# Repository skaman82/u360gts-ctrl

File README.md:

# u360gts-ctrl
u360gts Extension for the Mini-Case

This has the following functions:

• Turn ON/OFF the VTX</br>
• SmartAudio channel control (SA 2+ Version not supported, for unify nano you will need a 10k pull-down resistor on SA)</br>
• Battery monitoring</br>
• Controlls pan servo manually to allow to get to the screws of the case</br>
• Automatic parking mode to align the tracker again</br>

# PARTS
• Provided PCB

• Arduino Pro Micro (Leonardo) 3.3V
https://de.aliexpress.com/item/32992577032.html
If you have a 5V version, just replace the VREG on the board with this one: MIC5205-3.3YM5-TR

• 1206 4.7k resistor (R3)</br>
• 1206 27k resistor (R1)</br>
• 1206 100nf capacitor (C3)</br>
• 4x 0603 10k resistor (R2, R4, R5, R6)</br>
• 0603 1k resistor (R7)</br>
• IRLML6402 Mosfet (SOT23-3)</br>
• 2x BC848B Transistor (SOT23-3) (Q1, Q2)</br>

• 5-way tact switch
https://de.aliexpress.com/item/32860774374.html

• 128x32 I2C OLED Display
https://de.aliexpress.com/item/32965469301.html

• CD4066BM switch (SOP14 IC)
https://de.aliexpress.com/item/32461198916.html

• 3mm 940nm IR LEDs (receiver + transmitter) < 
receiver connects to GND and IR+ on the PCB; transmitter connects to 5v (through 100R resistor) and GND in the top box
https://de.aliexpress.com/item/32967272936.html

<strong>UPDATE 11. May 2020</strong><br>
Just spotted a bug on the PCB regarding the IR diode. I just corrected it in the new board file.
If you have the old version of the board, here is a workaround:<br><br>

• Remove R2 (don't throw it away)<br>
• bridge the two pads where R2 was sitting<br>
• solder the R2 to the outer side of the R6<br>
• connect 5V (BZ+) to the outer side of R2<br>
• Connect the IR LED (cathode on IR+, anode on IR-)<br>

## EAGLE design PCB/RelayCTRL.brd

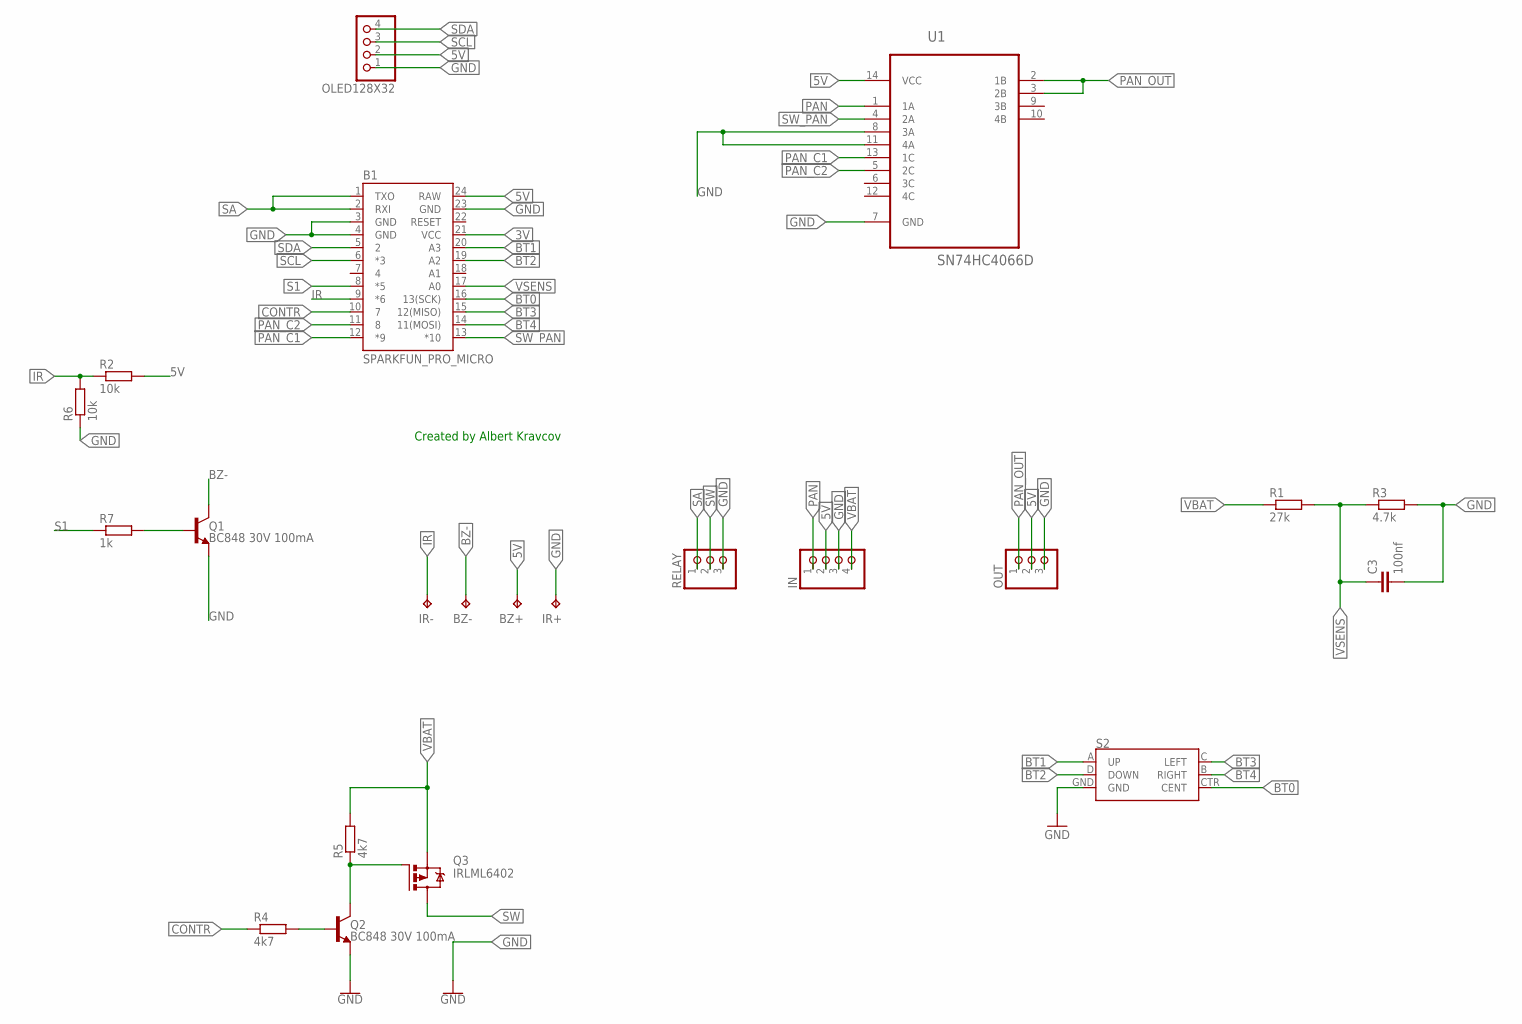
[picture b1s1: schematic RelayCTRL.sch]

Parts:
B1: SPARKFUN_PRO_MICRO
BZ+: TPTP15R; TP15R
BZ-: TPTP15R; TP15R
C3: 100nf; C1206
IN: PINHD-1X4; 1X04
IR+: TPTP15R; TP15R
IR-: TPTP15R; TP15R
OLED128X32: PINHD-1X4; 1X04
OUT: PINHD-1X3; 1X03
Q1, Q2: BC848 30V 100mA; SOT23-3
Q3: IRLML6402; MICRO3
R1: 27k; R1206
R2, R6: 10k; R0603
R3: 4.7k; R1206
R4, R5: 4k7; R0603
R7: 1k; R0603
RELAY: PINHD-1X3; 1X03
S2: JOYSTICK_MINI
U1: SN74HC4066D; SOIC127P600X175-14N

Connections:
3V: B1.21 (VCC)
5V: B1.24 (RAW), BZ+.TP, IN.2, OLED128X32.2, OUT.2, R2.2, U1.14 (VCC)
BT0: B1.16 (13(SCK)), S2.CTR (CENT)
BT1: B1.20 (A3), S2.A (UP)
BT2: B1.19 (A2), S2.D (DOWN)
BT3: B1.15 (12(MISO)), S2.C (LEFT)
BT4: B1.14 (11(MOSI)), S2.B (RIGHT)
BZ-: BZ-.TP, Q1.3 (C)
CONTR: B1.10 (7), R4.1
GND: B1.3 (GND), B1.4 (GND), B1.23 (GND), C3.2, IN.3, IR+.TP, OLED128X32.1, OUT.3, Q1.2 (E), Q2.2 (E), R3.2, R6.1, RELAY.3, S2.GND, U1.7 (GND), U1.8 (3A), U1.11 (4A)
IR: B1.9 (*6), IR-.TP, R2.1, R6.2
unnamed: Q2.1 (B), R4.2
unnamed: Q2.3 (C), Q3.1 (G), R5.1
unnamed: Q1.1 (B), R7.2
PAN: IN.1, U1.1 (1A)
PAN_C1: B1.12 (*9), U1.13 (1C)
PAN_C2: B1.11 (8), U1.5 (2C)
PAN_OUT: OUT.1, U1.2 (1B), U1.3 (2B)
S1: B1.8 (*5), R7.1
SA: B1.1 (TXO), B1.2 (RXI), RELAY.1
SCL: B1.6 (*3), OLED128X32.3
SDA: B1.5 (2), OLED128X32.4
SW: Q3.3 (D), RELAY.2
SW_PAN: B1.13 (*10), U1.4 (2A)
VBAT: IN.4, Q3.2 (S), R1.1, R5.2
VSENS: B1.17 (A0), C3.1, R1.2, R3.1

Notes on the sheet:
Created by Albert Kravcov

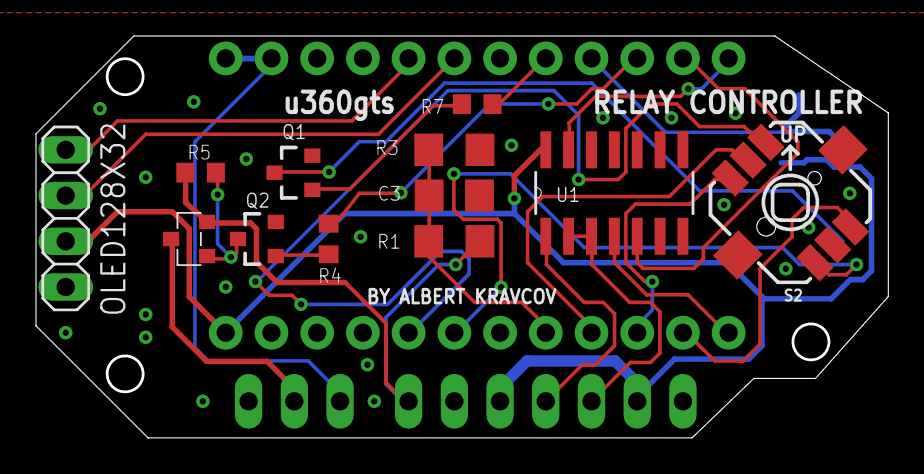
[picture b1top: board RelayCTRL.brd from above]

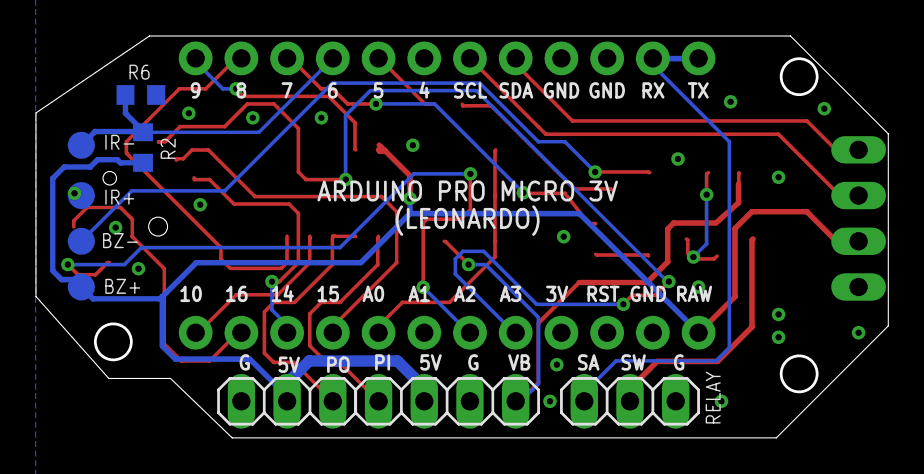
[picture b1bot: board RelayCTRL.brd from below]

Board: 2 copper layers, 47.2 x 22.2 mm, 22 parts (10 on the bottom side), 25 nets.

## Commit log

2020-02-07 Upload
2020-02-07 connection update
2020-02-07 image update
2020-02-07 image clarification
2020-02-07 fixed pcb error
2020-02-07 voltage callibration
2020-02-10 PCB Update
2020-05-02 some updates
2020-05-11 code improvements
2020-05-11 Corrected PCB bug (IR diode)
2020-05-12 cleanup
2020-05-14 Add correct target
2020-05-15 target notes
2020-05-15 First build log draft
2020-05-15 buld notes update
2020-05-19 update the build log
2020-05-20 adding thingiverse
2020-05-20 Added notes
2020-05-26 State LED
2020-07-09 Code Update
    • Two movement profiles for pan servos SERVO_SPT/SERVO_MG995
    • Cell count detection is more robust now
2020-07-27 pict upload

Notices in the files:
parts and their libraries:
SparkFun-Switches: Licensing: Creative Commons ShareAlike 4.0 International - https://creativecommons.org/licenses/by-sa/4.0
